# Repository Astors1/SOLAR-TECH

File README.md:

# SOLAR-TECH
PROYECTO (SEGUIDOR DE LUZ)

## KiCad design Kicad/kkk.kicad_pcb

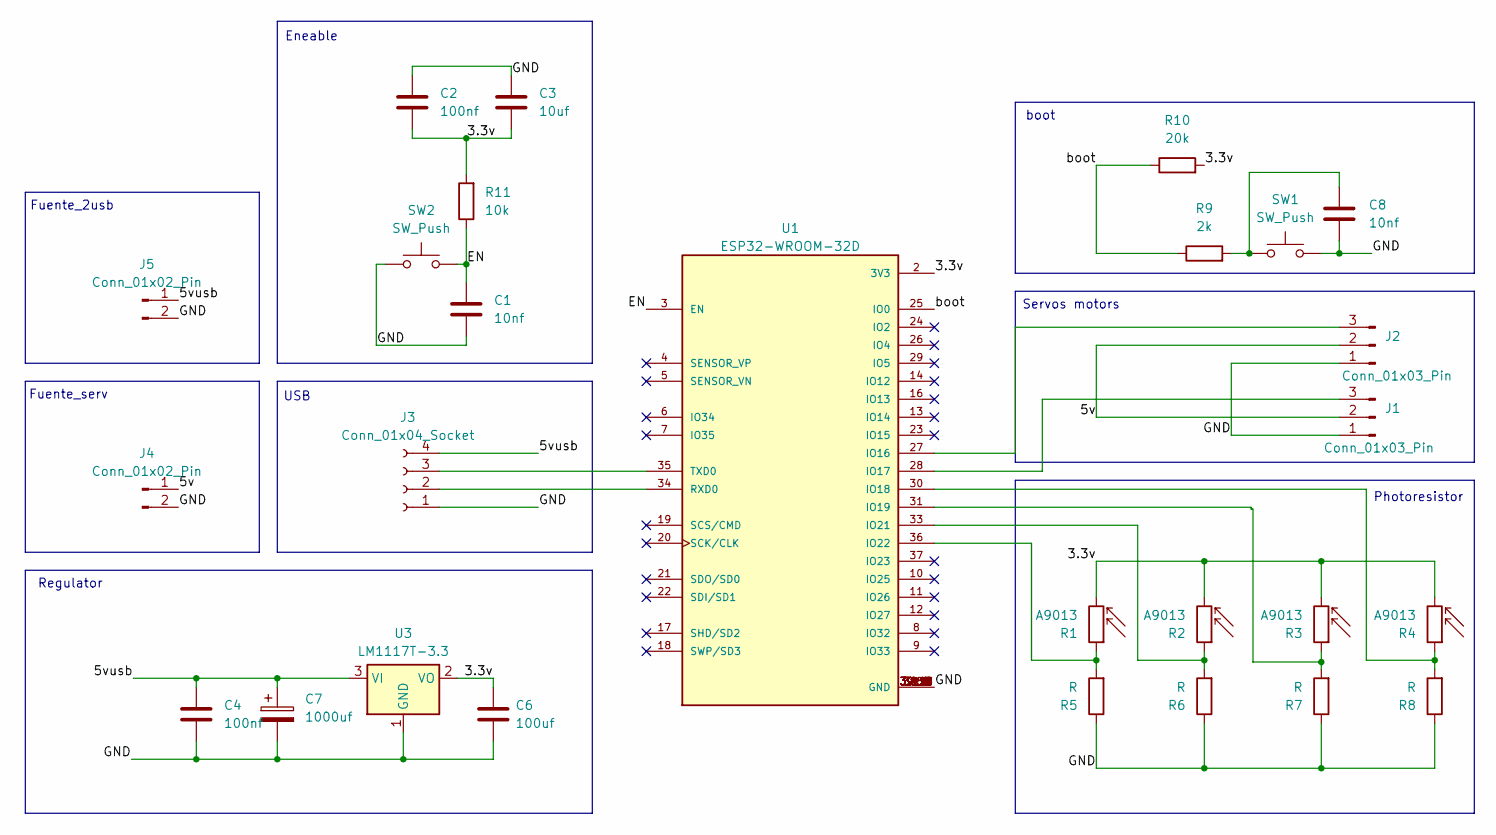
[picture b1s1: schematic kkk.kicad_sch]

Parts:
C1, C8: 10nf; CAP_0.1
C2, C4: 100nf; CAP_0.1
C3: 10uf; CAP_0.1
C6: 100uf; CP_Radial_D8.0mm_P3.50mm
C7: 1000uf; CP_Radial_D12.5mm_P5.00mm
J1, J2: Conn_01x03_Pin; PinHeader_1x03_P1.00mm_Vertical
J3: Conn_01x04_Socket; PinHeader_1x04_P1.00mm_Vertical
J4, J5: Conn_01x02_Pin; TerminalBlock_bornier-2_P5.08mm
R1, R2, R3, R4: A9013; PinHeader_1x02_P1.00mm_Vertical
R5, R6, R7, R8: R; rrr
R9: 2k; rrr
R10: 20k; rrr
R11: 10k; rrr
SW1, SW2: SW_Push; SW_TH_Tactile_Omron_B3F-10xx
U1: ESP32-WROOM-32D; MODULE_ESP32-WROOM-32D; PARTREV 1.9
U3: LM1117T-3.3; TO-220-3_Horizontal_TabDown

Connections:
/3.3v: C2.2, C3.2, C6.1, R1.2, R2.2, R3.2, R4.2, R10.2, R11.2, U1.2 (3V3), U3.2 (VO)
/5v: J1.2, J2.2, J4.1
/5vusb: C4.1, C7.1, J3.4, J5.1, U3.3 (VI)
/EN: C1.1, R11.1, SW2.2, U1.3 (EN)
/GND: C1.2, C2.1, C3.1, C4.2, C6.2, C7.2, C8.1, J1.1, J2.1, J3.1, J4.2, J5.2, R5.1, R6.1, R7.1, R8.1, SW1.2, SW2.1, U1.1 (GND), U1.15 (GND), U1.38 (GND), U1.39_1 (GND), U1.39_2 (GND), U1.39_3 (GND), U1.39_4 (GND), U1.39_5 (GND), U1.39_6 (GND), U1.39_7 (GND), U1.39_8 (GND), U1.39_9 (GND), U1.39_10 (GND), U1.39_11 (GND), U1.39_12 (GND), U1.39_13 (GND), U1.39_14 (GND), U1.39_15 (GND), U1.39_16 (GND), U1.39_17 (GND), U1.39_18 (GND), U1.39_19 (GND), U1.39_20 (GND), U1.39_21 (GND), U3.1 (GND)
/boot: R9.1, R10.1, U1.25 (IO0)
unnamed: C8.2, R9.2, SW1.1
unnamed: J1.3, U1.28 (IO17)
unnamed: J2.3, U1.27 (IO16)
unnamed: J3.2, U1.34 (RXD0)
unnamed: J3.3, U1.35 (TXD0)
unnamed: R4.1, R8.2, U1.30 (IO18)
unnamed: R3.1, R7.2, U1.31 (IO19)
unnamed: R2.1, R6.2, U1.33 (IO21)
unnamed: R1.1, R5.2, U1.36 (IO22)

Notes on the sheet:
Eneable
Regulator
Servos motors
Fuente_serv
Fuente_2usb
USB
boot
Photoresistor

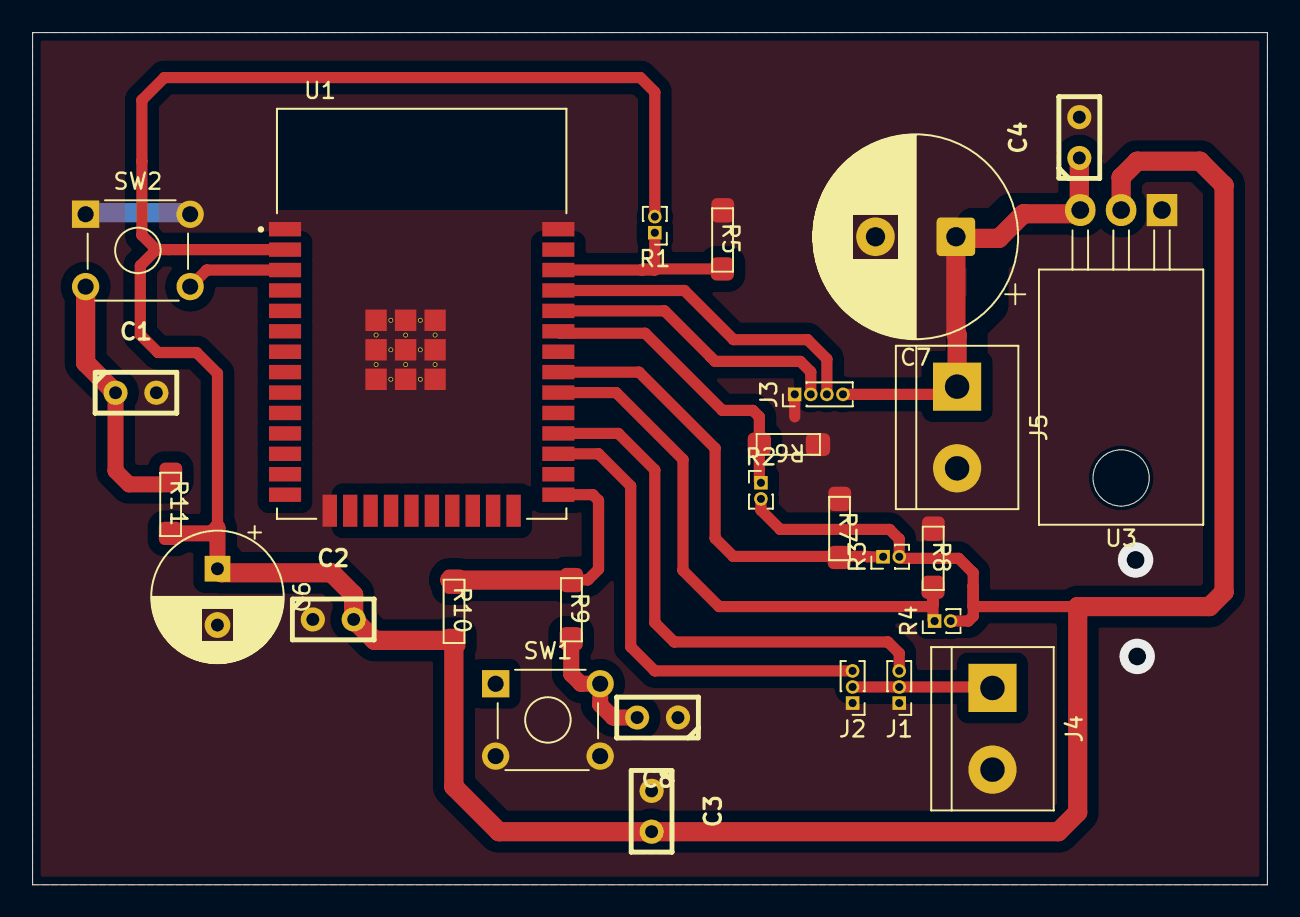
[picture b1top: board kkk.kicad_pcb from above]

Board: 2 copper layers, 76.8 x 53.0 mm, 27 parts (0 on the bottom side), 15 nets.

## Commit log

2025-05-15 Add files via upload
    Modelo 3D del panel solar (pieza por pieza)
2025-05-16 Crear Kicad
2025-05-16 Actualizar Kicad
2025-05-30 Create kicad
2025-10-20 Create pp
2025-11-03 Initialize servos and implement basic movement
2025-11-07 Fix syntax error in variable declaration
2025-11-17 Implement vertical and horizontal servo control
    Refactor servo control to include vertical and horizontal movement based on LDR readings.
